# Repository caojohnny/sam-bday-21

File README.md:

# `sam-bday-21`

PCB I designed as a gift for my roommate's 21st birthday.

It's an LED flasher using an astable 555 chip and powered off an AA battery.
The aesthetic design is two antennas on the silkscreen since he's interested
in RF.

# Problems

I stayed up late on the design so there is a number of major design problems
with the board, the main ones documented on the schematic which can be found
in the `preview/` folder.

On the schematic side, I forgot to change the 10u cap on the 555 to 15u and
ended up ordering the wrong value, so the LEDs alternate at around 600 ms as
opposed to the full 1 second I was hoping that it would. The second major error
was the resistors were not sized correctly because I misinterpreted the I-V
curves on the LED datasheets; they should have been double the size. This
results in around 500 mA current draw which I did not design the layout to
handle.

On the layout, the transistor footprint was completely wrong, I read the
datasheet as having a SOT-89 as opposed to the "SC-89" which is a SOT-416. 
This was bodged onto the PCB by rotating the transistor and using a wire to
connect the gate around the footprint. The main goal on the front side was to
avoid as much copper as possible for aesthetic reasons, but this lead to me
not utilizing a 5V plane on the front, which ended up being just unclean and
reduces the thermal dissipation for the LEDs. The backside was not designed
very cleanly and the trace widths are not properly sized in a number of
locations. Finally, there is awful noise on the output of the 555 which I
haven't investigated, but it appears not to affect function.

Overall, the board behaves correctly at the wrong frequency, but it still does
relatively close to what I designed it to do.

# Software

[KiCad](https://www.kicad.org/)

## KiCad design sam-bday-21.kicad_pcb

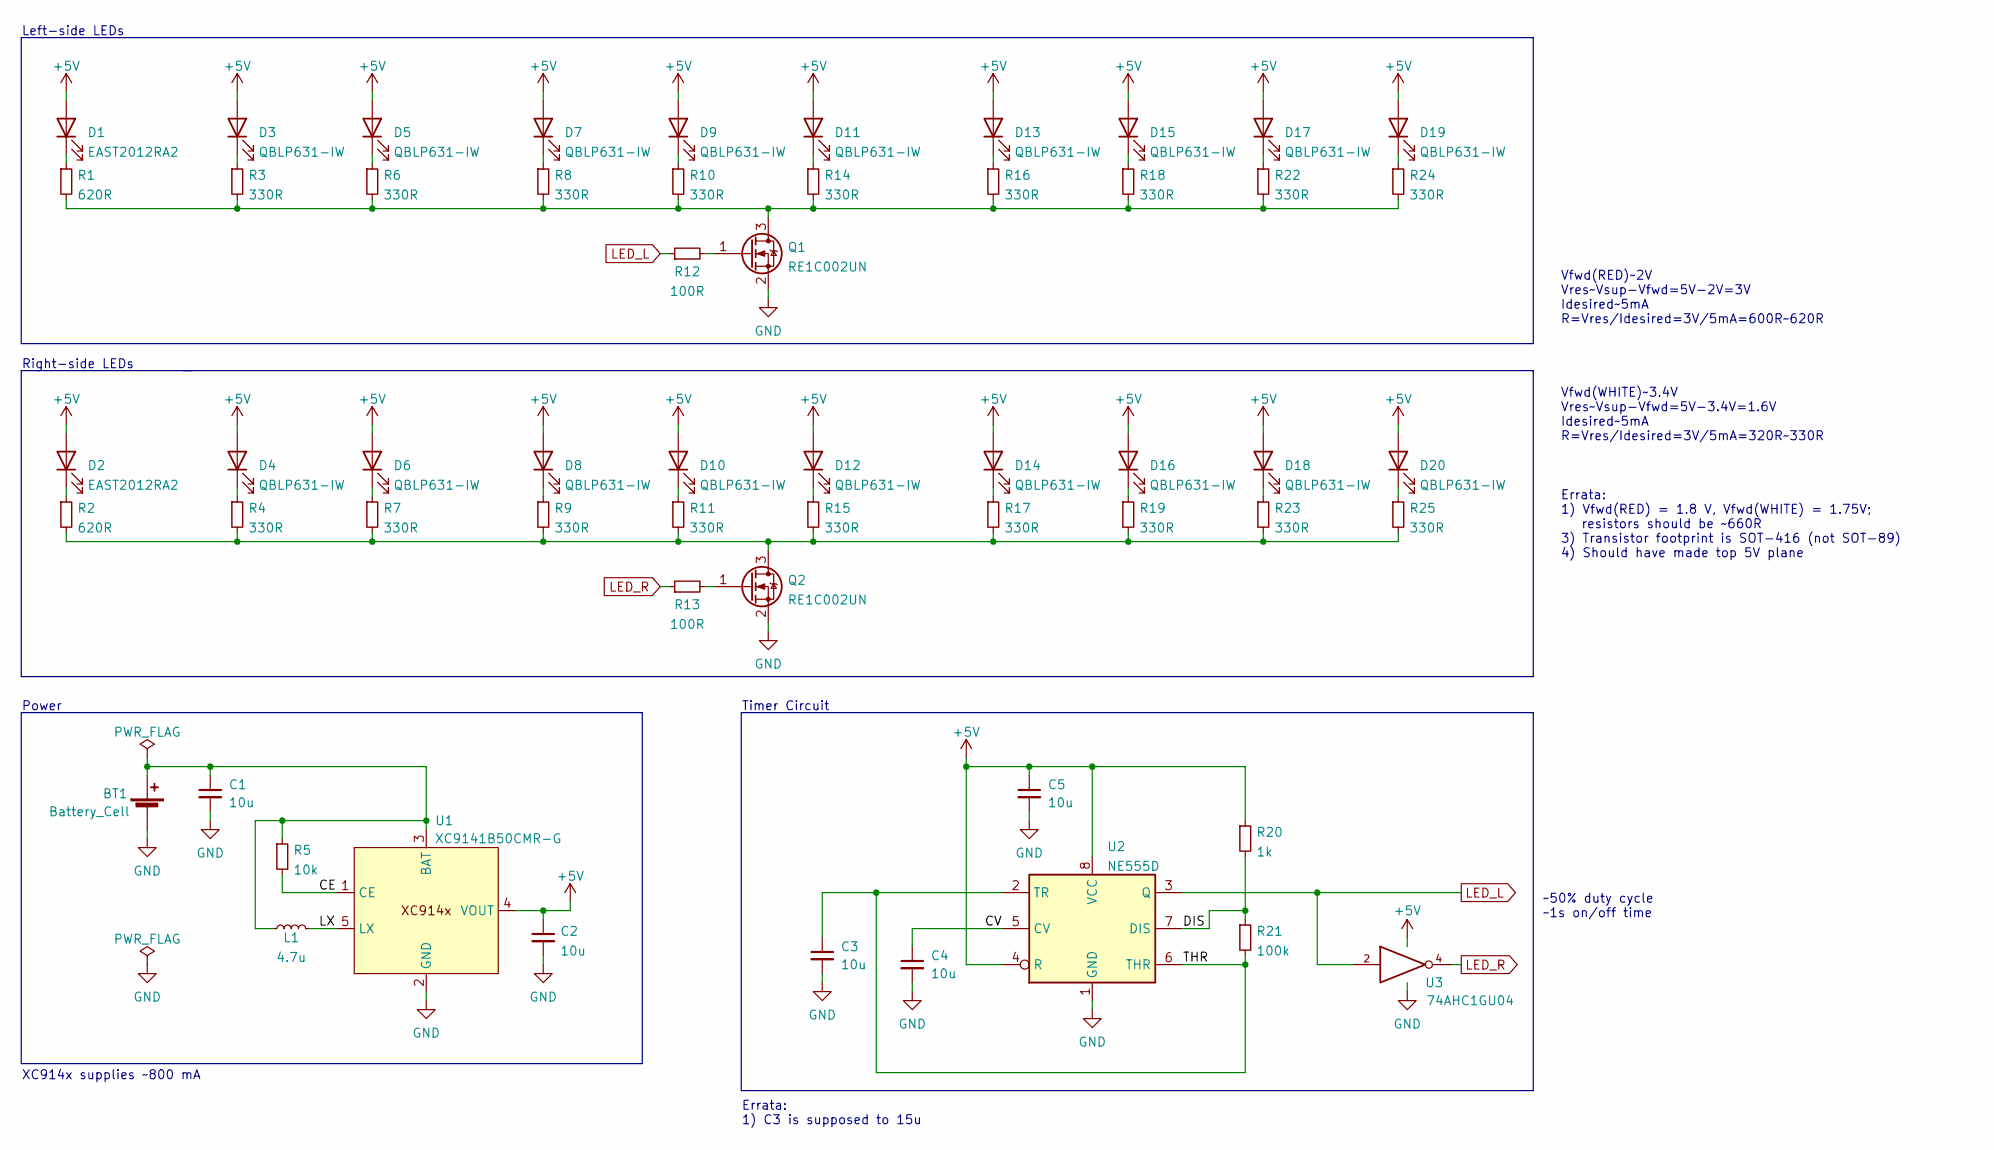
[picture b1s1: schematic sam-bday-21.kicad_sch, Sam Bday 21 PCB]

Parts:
BT1: Battery_Cell; BatteryHolder_Keystone_2460_1xAA
C1, C2, C3, C4, C5: 10u; C_0603_1608Metric
D1, D2: EAST2012RA2; LED_0805_2012Metric
D3, D4, D5, D6, D7, D8, D9, D10, D11, D12, D13, D14, D15, D16, D17, D18, D19, D20: QBLP631-IW; LED_0805_2012Metric
L1: 4.7u; L_0805_2012Metric
Q1, Q2: RE1C002UN; SOT-89-3
R1, R2: 620R; R_0603_1608Metric
R3, R4, R6, R7, R8, R9, R10, R11, R14, R15, R16, R17, R18, R19, R22, R23, R24, R25: 330R; R_0603_1608Metric
R5: 10k; R_0603_1608Metric
R12, R13: 100R; R_0603_1608Metric
R20: 1k; R_0603_1608Metric
R21: 100k; R_0603_1608Metric
U1: XC9141B50CMR-G; SOT-23-5
U2: NE555D; SOIC-8_3.9x4.9mm_P1.27mm
U3: 74AHC1GU04; SOT-353_SC-70-5

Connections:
+5V: C2.1, C5.1, D1.2 (A), D2.2 (A), D3.2 (A), D4.2 (A), D5.2 (A), D6.2 (A), D7.2 (A), D8.2 (A), D9.2 (A), D10.2 (A), D11.2 (A), D12.2 (A), D13.2 (A), D14.2 (A), D15.2 (A), D16.2 (A), D17.2 (A), D18.2 (A), D19.2 (A), D20.2 (A), R20.1, U1.4 (VOUT), U2.4 (R), U2.8 (VCC), U3.5 (VCC)
/CE: R5.2, U1.1 (CE)
/CV: C4.1, U2.5 (CV)
/DIS: R20.2, R21.1, U2.7 (DIS)
/LX: L1.2, U1.5 (LX)
/THR: C3.1, R21.2, U2.2 (TR), U2.6 (THR)
GND: BT1.2 (-), C1.2, C2.2, C3.2, C4.2, C5.2, Q1.2 (S), Q2.2 (S), U1.2 (GND), U2.1 (GND), U3.3 (GND)
LED_L: R12.1, U2.3 (Q), U3.2
LED_R: R13.1, U3.4
unnamed: BT1.1 (+), C1.1, L1.1, R5.1, U1.3 (BAT)
unnamed: D1.1 (K), R1.1
unnamed: D2.1 (K), R2.1
unnamed: D3.1 (K), R3.1
unnamed: D4.1 (K), R4.1
unnamed: D5.1 (K), R6.1
unnamed: D6.1 (K), R7.1
unnamed: D7.1 (K), R8.1
unnamed: D8.1 (K), R9.1
unnamed: D9.1 (K), R10.1
unnamed: D10.1 (K), R11.1
unnamed: D11.1 (K), R14.1
unnamed: D12.1 (K), R15.1
unnamed: D13.1 (K), R16.1
unnamed: D14.1 (K), R17.1
unnamed: D15.1 (K), R18.1
unnamed: D16.1 (K), R19.1
unnamed: D17.1 (K), R22.1
unnamed: D18.1 (K), R23.1
unnamed: D19.1 (K), R24.1
unnamed: D20.1 (K), R25.1
unnamed: Q1.1 (G), R12.2
unnamed: Q1.3 (D), R1.2, R3.2, R6.2, R8.2, R10.2, R14.2, R16.2, R18.2, R22.2, R24.2
unnamed: Q2.1 (G), R13.2
unnamed: Q2.3 (D), R2.2, R4.2, R7.2, R9.2, R11.2, R15.2, R17.2, R19.2, R23.2, R25.2

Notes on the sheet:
Vfwd(WHITE)~3.4V Vres~Vsup-Vfwd=5V-3.4V=1.6V Idesired~5mA R=Vres/Idesired=3V/5mA=320R~330R
Right-side LEDs
Left-side LEDs
XC914x supplies ~800 mA
Timer Circuit
Vfwd(RED)~2V Vres~Vsup-Vfwd=5V-2V=3V Idesired~5mA R=Vres/Idesired=3V/5mA=600R~620R
Power
~50% duty cycle ~1s on/off time
Errata: 1) Vfwd(RED) = 1.8 V, Vfwd(WHITE) = 1.75V; resistors should be ~660R 3) Transistor footprint is SOT-416 (not SOT-89) 4) Should have made top 5V plane
Errata: 1) C3 is supposed to 15u

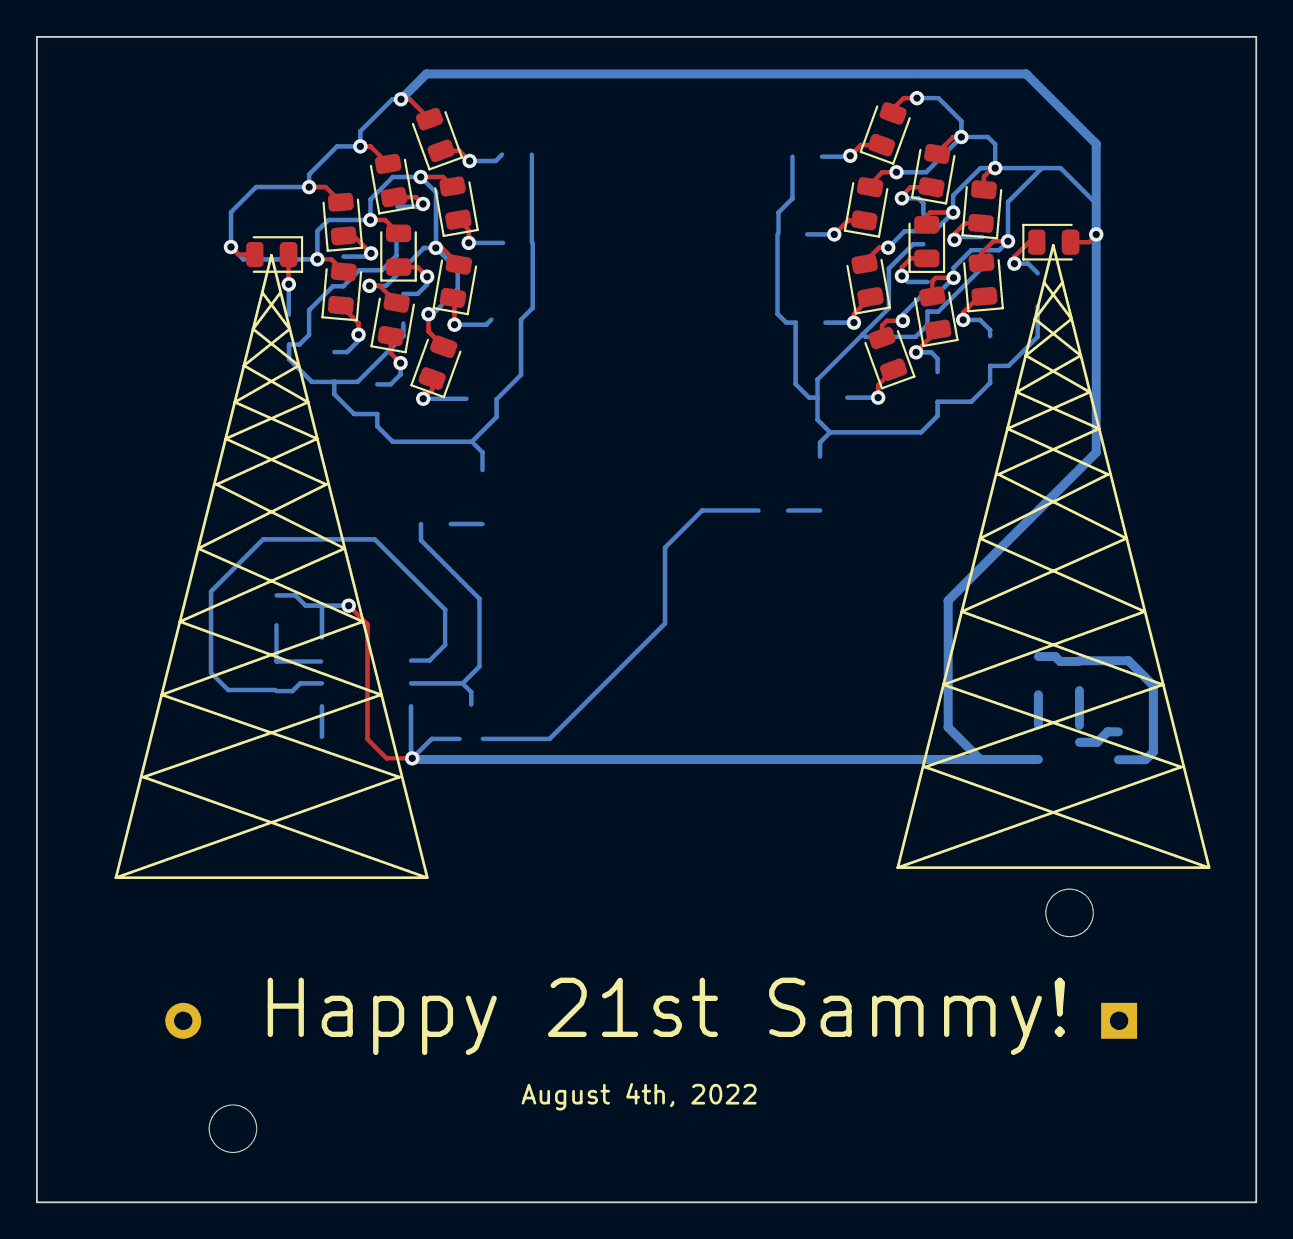
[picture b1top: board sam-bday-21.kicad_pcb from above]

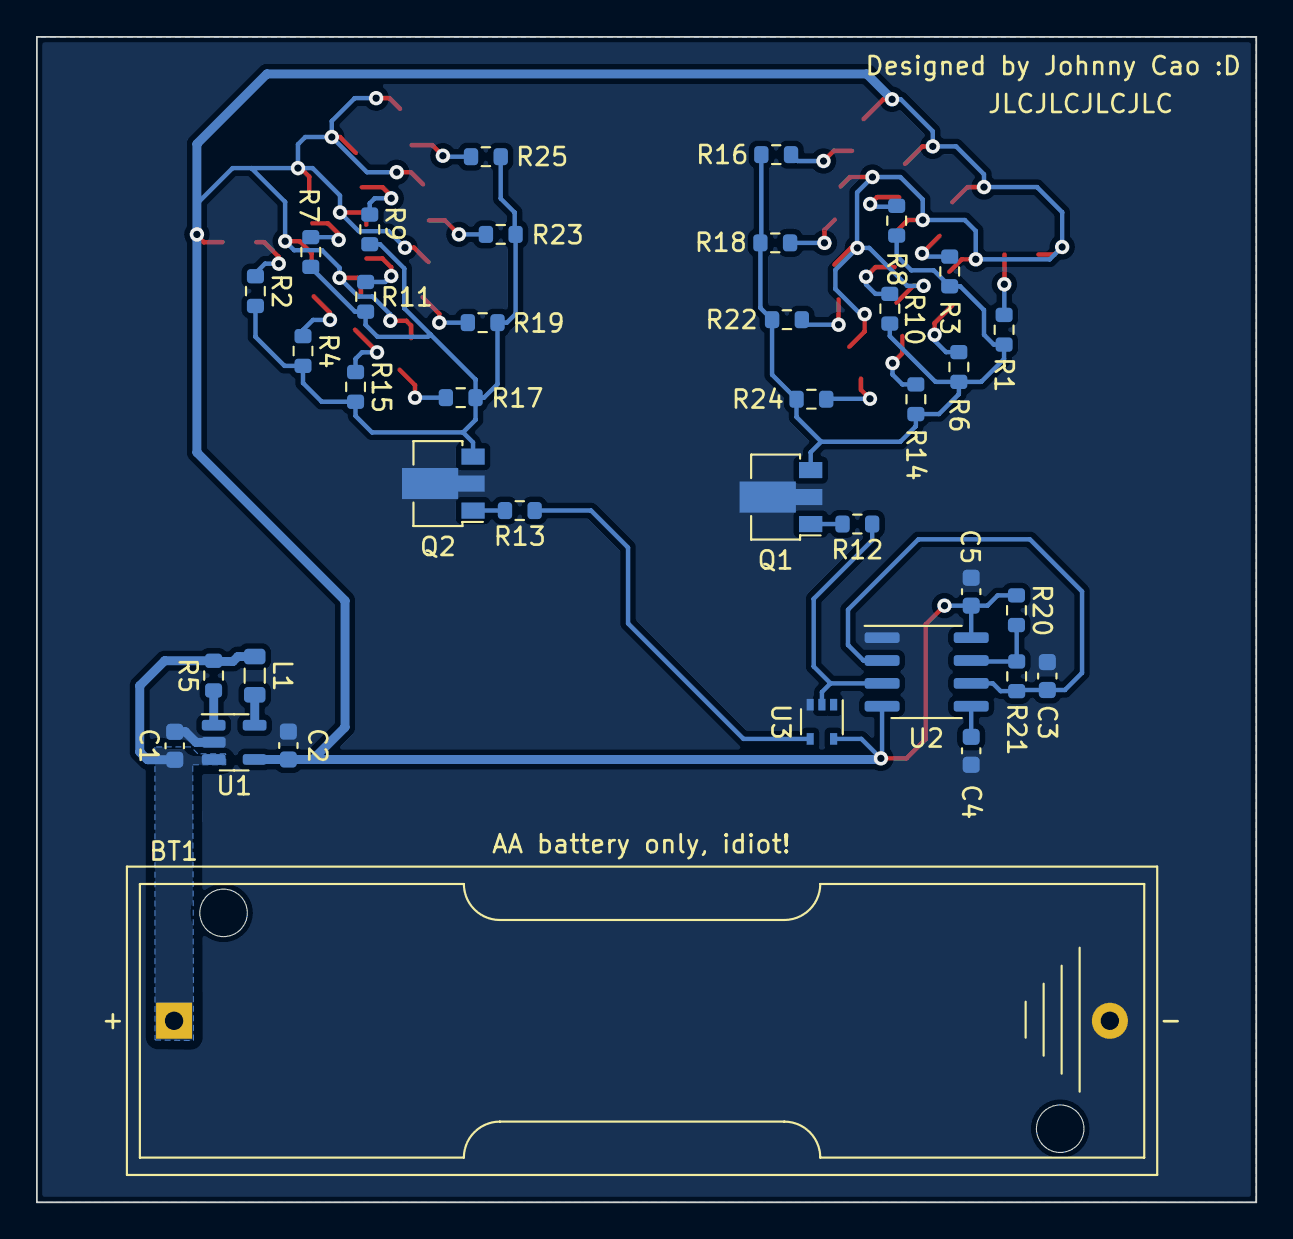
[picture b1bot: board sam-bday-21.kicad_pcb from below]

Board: 2 copper layers, 67.7 x 64.7 mm, 57 parts (37 on the bottom side), 34 nets.
